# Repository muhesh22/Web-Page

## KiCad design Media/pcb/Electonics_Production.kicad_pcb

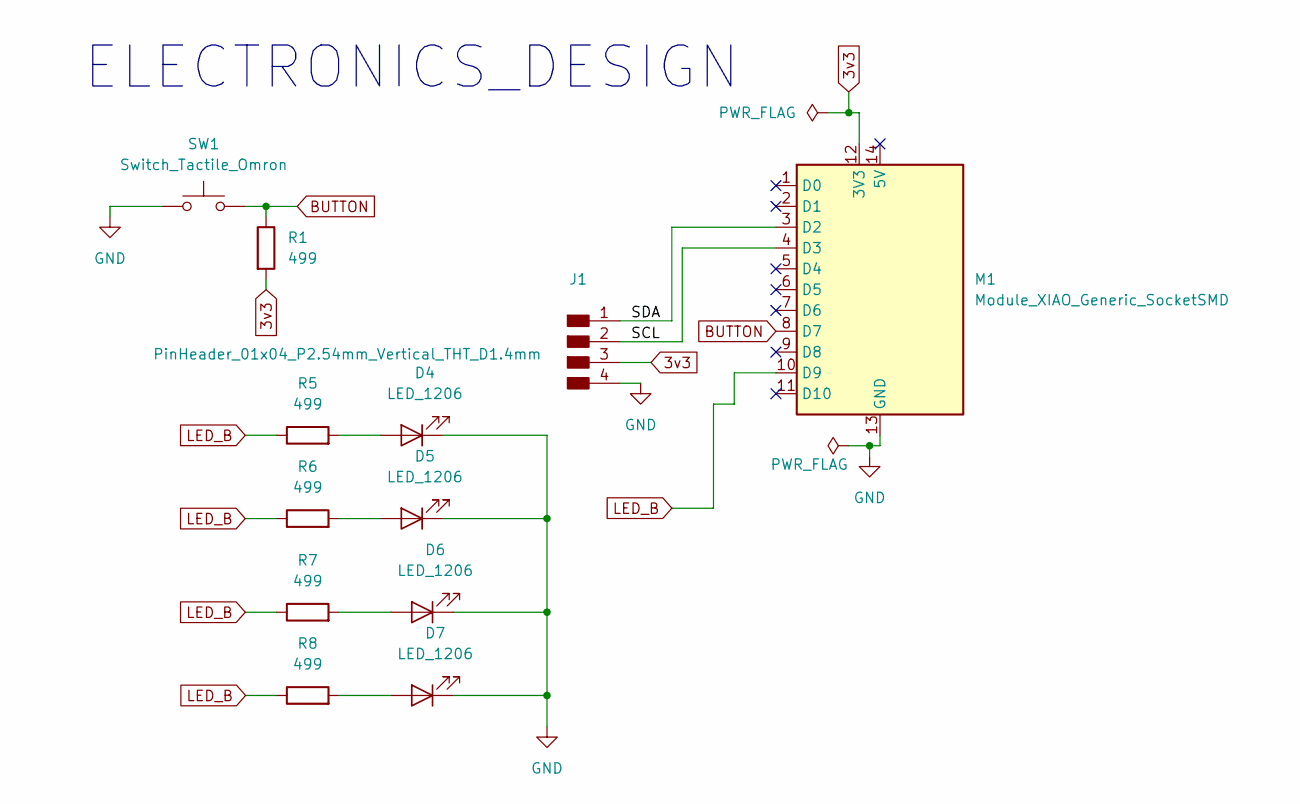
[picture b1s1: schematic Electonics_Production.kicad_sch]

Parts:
D4, D5, D6, D7: LED_1206
J1: PinHeader_01x04_P2.54mm_Vertical_THT_D1.4mm; PinHeader_01x04_P2.54mm_Horizontal_SMD
M1: Module_XIAO_Generic_SocketSMD
R1, R5, R6, R7, R8: 499; R_1206
SW1: Switch_Tactile_Omron; Button_Omron_B3SN_6.0x6.0mm

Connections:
3v3: J1.3, M1.12 (3V3), R1.2
/SCL: J1.2, M1.4 (D3)
/SDA: J1.1, M1.3 (D2)
BUTTON: M1.8 (D7), R1.1, SW1.2
GND: D4.1 (K), D5.1 (K), D6.1 (K), D7.1 (K), J1.4, M1.13 (GND), SW1.1
LED_B: M1.10 (D9), R5.1, R6.1, R7.1, R8.1
unnamed: D4.2 (A), R5.2
unnamed: D5.2 (A), R6.2
unnamed: D6.2 (A), R7.2
unnamed: D7.2 (A), R8.2

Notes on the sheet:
ELECTRONICS_DESIGN

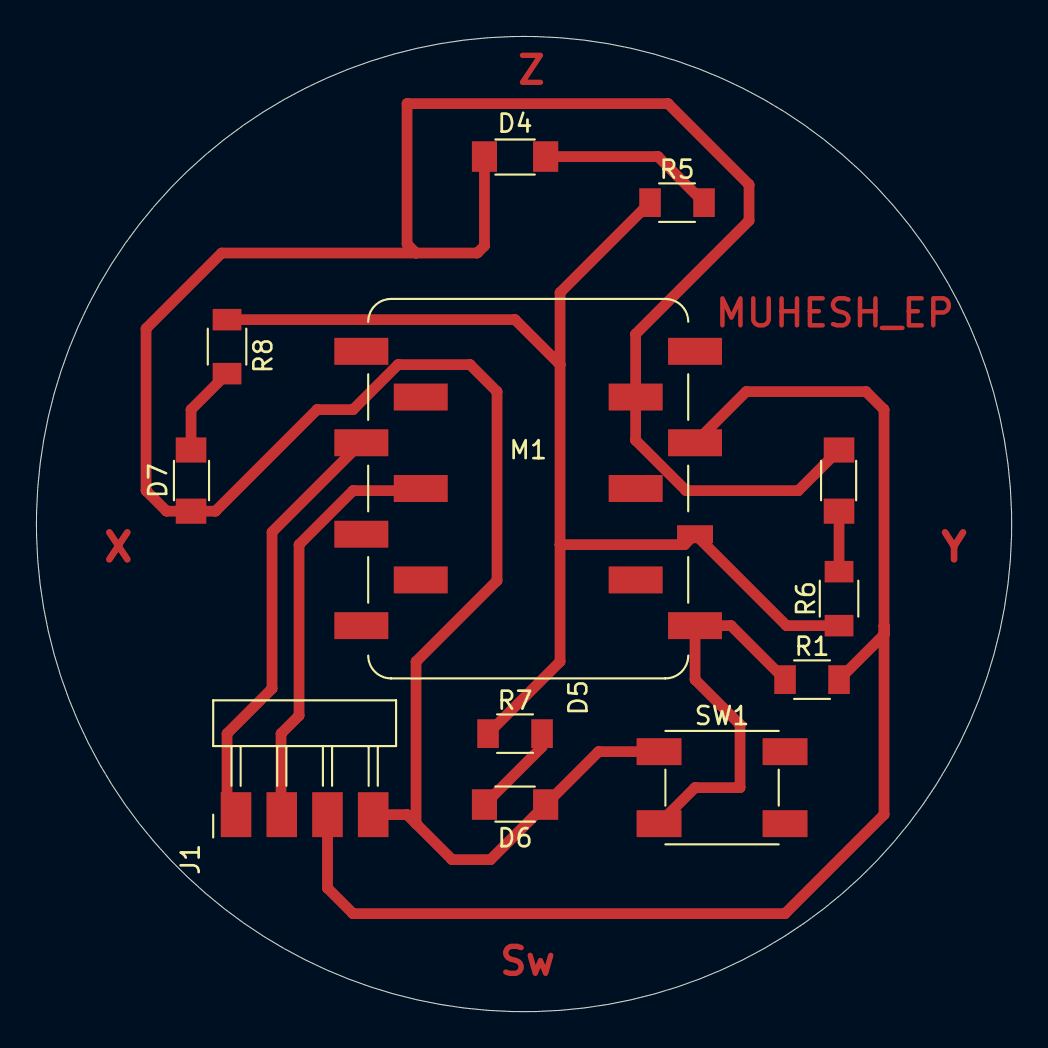
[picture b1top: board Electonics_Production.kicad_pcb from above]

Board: 2 copper layers, 54.2 x 54.2 mm, 12 parts (0 on the bottom side), 10 nets.

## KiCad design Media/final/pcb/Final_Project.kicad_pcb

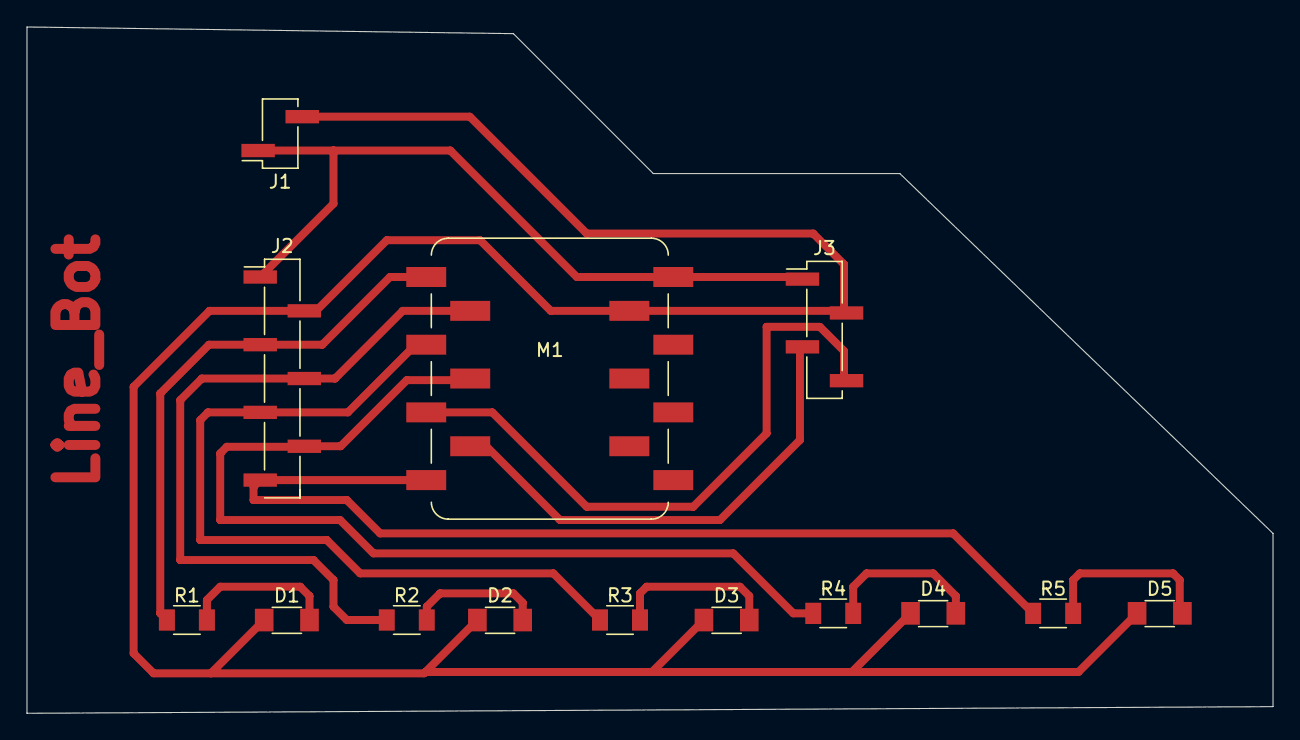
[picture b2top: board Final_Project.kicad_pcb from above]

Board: 2 copper layers, 93.5 x 51.5 mm, 14 parts (0 on the bottom side), 14 nets.

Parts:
D1, D2, D3, D4, D5: LED_1206
J1: PinHeader_01x02_P2.54mm_Horizontal_SMD; PinHeader_1x02_P2.54mm_Vertical_SMD_Pin1Right
J2: PinHeader_01x07_P2.54mm_Horizontal_SMD; PinHeader_1x07_P2.54mm_Vertical_SMD_Pin1Left
J3: PinHeader_01x04_P2.54mm_Horizontal_SMD; PinHeader_1x04_P2.54mm_Vertical_SMD_Pin1Left
M1: Module_XIAO_Generic_SocketSMD
R1, R2, R3, R4, R5: R_1206

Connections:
5V: J1.1, J2.1, J3.1, M1.14 (5V)
A0: J2.3, M1.1 (D0), R1.1
A1: J2.4, M1.2 (D1), R2.1
A2: J2.5, M1.3 (D2), R3.1
A3: J2.6, M1.4 (D3), R4.1
A4: J2.7, M1.7 (D6), R5.1
GND: D1.1 (K), D2.1 (K), D3.1 (K), D4.1 (K), D5.1 (K), J1.2, J2.2, J3.2, M1.13 (GND)
unnamed: D1.2 (A), R1.2
unnamed: D2.2 (A), R2.2
unnamed: D3.2 (A), R3.2
unnamed: D4.2 (A), R4.2
unnamed: D5.2 (A), R5.2
SCL: J3.3, M1.6 (D5)
SDA: J3.4, M1.5 (D4)

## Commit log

2025-04-20 Windows
2025-04-23 Trichy Work
